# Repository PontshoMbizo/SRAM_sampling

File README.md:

# SRAM_sampling

Passive capture of address and data from a legacy battery-backed SRAM (M48T35), on a MAX10 (DE10-Lite) FPGA. The SRAM only presents valid data for about 10 ns, roughly 70 ns after chip enable and output enable go low. The FPGA times that window with a 200 MHz clock and latches address and data inside it, without loading the bus.

## The problem

A legacy embedded control system boots from a non-volatile SRAM whose backup battery will eventually die, taking the boot and configuration data with it. The contents have to be read out without disturbing the host that owns the bus, which means sampling the address and data lines in step with the host's own accesses.

## Design

```mermaid
flowchart LR
    SRAM[5 V SRAM bus] --> BUF[8-bit bus buffers 5 V to 3.3 V]
    BUF --> SYNC[2-flop synchroniser E, O]
    SYNC --> TMR[4-bit timer, 5 ns tick]
    SYNC --> RD[read = E low, O low, count >= 12]
    TMR --> RD
    PLL[PLL 50 to 200 MHz] --> TMR
    RD --> LATCH[rising-edge latch address and data]
    BUF --> LATCH
```

| Block | Choice | Why |
|---|---|---|
| Clock | PLL, 50 MHz to 200 MHz | 5 ns resolution on a 10 ns window |
| Timer | 4-bit, saturates at 15, held at 0 while E or O is high | Counts from the real start of each access and gives one strobe per access |
| Synchroniser | Two flops on E and O | E and O come from another clock domain; the timer and strobe never see a raw edge |
| Read strobe | E low, O low, count at least 12 | 12 ticks plus the two synchroniser cycles lands the latch at about 72 to 75 ns |
| Latch | Rising edge of the strobe | Address and data captured on the same edge |
| Interface | 8-bit bus buffers | 5 V SRAM side, 3.3 V FPGA I/O, no contention on the bus |

## Findings

Simulated with Icarus Verilog against a testbench that asserts E/O at 16 different offsets inside the timer period and drives valid data 70 to 80 ns later.

| Design | Offsets that latch the right data | Read strobe, ns after E/O low |
|---|---|---|
| Original (timer reset once at start-up) | 2 of 16 | 0 to 67.5, depends on timer phase |
| Fixed (timer re-armed per access, synchronised inputs) | 16 of 16 | 69.5, every offset |

The original timer ran freely, so the strobe landed wherever the timer happened to be when E/O dropped. The first version of the testbench hid this because it asserted E/O at t = 0, when the timer was aligned. A later access in the same testbench was captured only 27.5 ns after assertion, before the data was valid.

## Run the simulation

```bash
cd firmware/simulations/src
iverilog -g2005 -o sim sample_tb.v sample.v read.v read_data.v timer_5ns.v && vvp sim      # waveform dump
iverilog -g2005 -o sweep phase_sweep_tb.v sample.v read.v read_data.v timer_5ns.v && vvp sweep   # 16 of 16 check
```

For the board build, open `firmware/src/sample.qpf` in Quartus Prime Lite (device 10M50DAF484C7G). Setup notes are in [SETUP.md](SETUP.md).

## Limits

- Verified in simulation only. The synchroniser and the count of 12 are chosen from the simulated 70 to 80 ns window and have not been timed against the real SRAM on a board.
- Capture only: there is no output interface. `output_DATA` and `output_ADDR` are registered values for observation, and nothing transmits them.
- One access is latched per E/O assertion. Back-to-back accesses with E/O held low between them are not separated.
- The timing numbers assume the 70 ns access time quoted for this part.

## Layout

```
firmware/src/                 Quartus project and synthesisable sources
firmware/simulations/src/     testbenches and simulation copy of the top level
hardware/SRAM_interface/      KiCad 9 schematic and PCB for the level-shifting interface
```

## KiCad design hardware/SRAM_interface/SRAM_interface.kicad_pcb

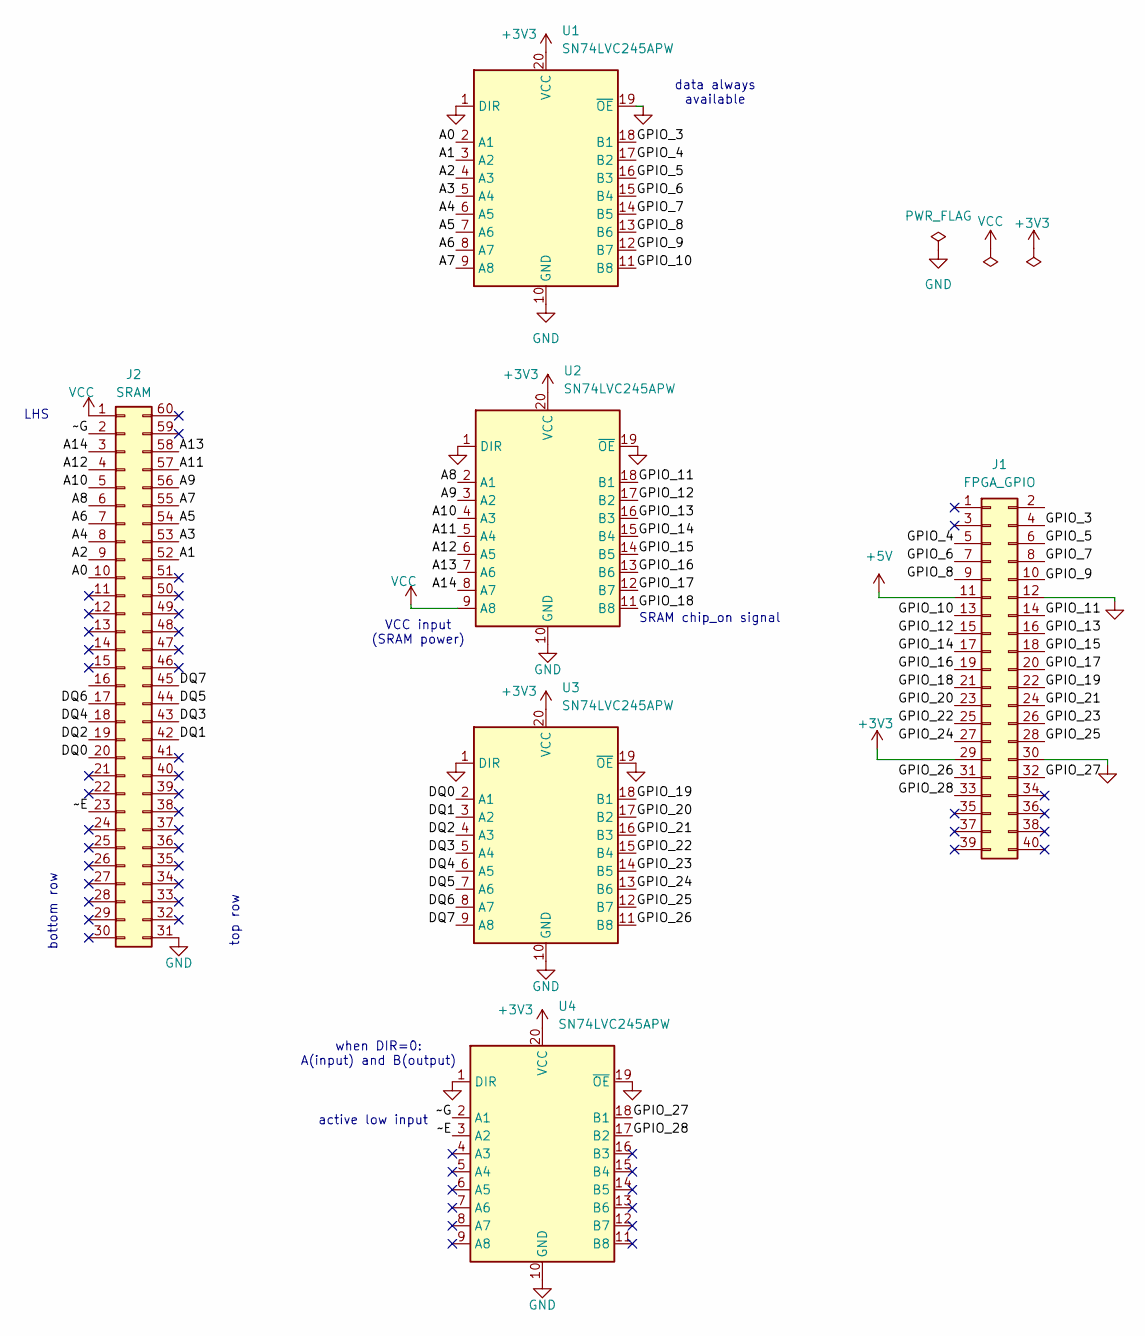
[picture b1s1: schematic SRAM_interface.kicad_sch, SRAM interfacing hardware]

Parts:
J1: FPGA_GPIO; IDC-Header_2x20_P2.54mm_Vertical
J2: SRAM; IDC-Header_2x30_P2.54mm_Vertical
U1, U2, U3, U4: SN74LVC245APW; TSSOP-20_4.4x6.5mm_P0.65mm

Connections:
+3V3: J1.29, U1.20 (VCC), U2.20 (VCC), U3.20 (VCC), U4.20 (VCC)
+5V: J1.11
/A0: J2.10, U1.2 (A1)
/A1: J2.52, U1.3 (A2)
/A2: J2.9, U1.4 (A3)
/A3: J2.53, U1.5 (A4)
/A4: J2.8, U1.6 (A5)
/A5: J2.54, U1.7 (A6)
/A6: J2.7, U1.8 (A7)
/A7: J2.55, U1.9 (A8)
/A8: J2.6, U2.2 (A1)
/A9: J2.56, U2.3 (A2)
/A10: J2.5, U2.4 (A3)
/A11: J2.57, U2.5 (A4)
/A12: J2.4, U2.6 (A5)
/A13: J2.58, U2.7 (A6)
/A14: J2.3, U2.8 (A7)
/DQ0: J2.20, U3.2 (A1)
/DQ1: J2.42, U3.3 (A2)
/DQ2: J2.19, U3.4 (A3)
/DQ3: J2.43, U3.5 (A4)
/DQ4: J2.18, U3.6 (A5)
/DQ5: J2.44, U3.7 (A6)
/DQ6: J2.17, U3.8 (A7)
/DQ7: J2.45, U3.9 (A8)
/GPIO_3: J1.4, U1.18 (B1)
/GPIO_4: J1.5, U1.17 (B2)
/GPIO_5: J1.6, U1.16 (B3)
/GPIO_6: J1.7, U1.15 (B4)
/GPIO_7: J1.8, U1.14 (B5)
/GPIO_8: J1.9, U1.13 (B6)
/GPIO_9: U1.12 (B7)
/GPIO_10: J1.13, U1.11 (B8)
/GPIO_11: J1.14, U2.18 (B1)
/GPIO_12: J1.15, U2.17 (B2)
/GPIO_13: J1.16, U2.16 (B3)
/GPIO_14: J1.17, U2.15 (B4)
/GPIO_15: J1.18, U2.14 (B5)
/GPIO_16: J1.19, U2.13 (B6)
/GPIO_17: J1.20, U2.12 (B7)
/GPIO_18: J1.21, U2.11 (B8)
/GPIO_19: J1.22, U3.18 (B1)
/GPIO_20: J1.23, U3.17 (B2)
/GPIO_21: J1.24, U3.16 (B3)
/GPIO_22: J1.25, U3.15 (B4)
/GPIO_23: J1.26, U3.14 (B5)
/GPIO_24: J1.27, U3.13 (B6)
/GPIO_25: J1.28, U3.12 (B7)
/GPIO_26: J1.31, U3.11 (B8)
/GPIO_27: J1.32, U4.18 (B1)
/GPIO_28: J1.33, U4.17 (B2)
/~E: J2.23, U4.3 (A2)
/~G: J2.2, U4.2 (A1)
GND: J1.12, J1.30, J2.31, U1.1 (DIR), U1.10 (GND), U1.19 (~OE), U2.1 (DIR), U2.10 (GND), U2.19 (~OE), U3.1 (DIR), U3.10 (GND), U3.19 (~OE), U4.1 (DIR), U4.10 (GND), U4.19 (~OE)
VCC: J2.1, U2.9 (A8)

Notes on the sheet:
when DIR=0: A(input) and B(output)
VCC input (SRAM power)
bottom row
top row
LHS
SRAM chip_on signal
active low input
data always available

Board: 2 copper layers, 6 parts (0 on the bottom side), 53 nets, no tracks yet.

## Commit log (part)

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2025-07-17 Initial commit for SRAM sampling project
2025-07-17 added a /src/ directory
2025-07-17 added a README and a project SETUP .md files
2025-07-18 clean project with a .gitignore for all the log and compilation files
2025-07-21 main program structure
2025-07-24 working simulations and included hardware_interface schematic
2025-07-25 pin mapping complete, imported to PCB Editor
2025-07-28 final commit?
